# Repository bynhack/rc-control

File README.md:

# rc-control

**English** | [繁體中文](README.zh-TW.md) | [简体中文](README.zh-CN.md)

Drive RC cars with a sim-racing wheel and pedals. Plug the wheel into a 7" ESP32-P4 touch screen: it reads the wheel over USB, runs a driving model with ignition, gears, coasting and a real brake, and sends the result to the car over the radio that car uses. You don't need a PC.

## Features

- **Standalone wheel controller.** Built on the ESP32-P4 7" touch board with a MOZA R5 or Thrustmaster T300RS wheel base, picked on the screen.
- **Three ways to reach the car**, chosen per car:
  - ExpressLRS (CRSF)
  - a 4-in-1 MULTI module, over its serial protocol or as PPM
  - the toy car's own stock remote, with its pots driven by a DAC
- **Per-car handling** that every radio goes through. You set the steering range, expo, steering and throttle dead bands, trim, end points and reverse on the wheel itself.
- **Driving like a car.** Ignition, gears R N 1 2 3, coasting, a real brake, and an automatic brake-then-reverse sequence for the ESC.
- **Force feedback** on both bases (USB PID on the MOZA, Thrustmaster's protocol on the T300). Centring gets stronger with speed, and a soft stop marks the steering lock.
- **Dashboard.** Two instrument clusters with Simplified and Traditional Chinese text, six car profiles, and engine sound synthesised live on the board's speaker.
- **The car side.** The X2201's main board (KiCad: ESP32-S3, a brushed ESC and a 5 V BEC on board, push-button power), IR lap transponders and a finish-line arch, and 3D-printable parts for the wheel stand and the car.

## Documentation

| | |
|---|---|
| [Wheel controller](docs/en/wheel-controller.md) | Hardware, wiring, building and flashing the firmware |
| [Driving and handling](docs/en/driving.md) | Buttons, the driving model, cars, the handling settings, force feedback |
| [Radios](docs/en/radios.md) | ExpressLRS, MULTI 4-in-1, the toy remote |
| [Converting a toy remote](docs/en/toy-remote.md) | Driving a toy car's stock remote with an MCP4728 DAC |
| [Hardware](docs/en/hardware.md) | 3D-printed parts and the X2201 main board |
| [Lap-timing arch](docs/en/lap-arch.md) | The finish-line arch: receivers, wiring, firmware, lap events |
| [Development](docs/en/development.md) | Code layout, serial console, tuning page, regenerating fonts and assets |

## Quick start

```bash
git clone https://github.com/bynhack/rc-control.git
cd rc-control/firmware/wheel-controller
. ~/esp/esp-idf/export.sh          # ESP-IDF v5.5
idf.py build
idf.py -p /dev/cu.usbmodemXXXX flash
```

Then wire up a radio ([Radios](docs/en/radios.md)), plug the wheel into the board's USB-A port, and press Start on the wheel to start the engine.

## Repository layout

```
firmware/
  wheel-controller/     the wheel controller on the ESP32-P4 (ESP-IDF, C)
    main/               firmware source
    tools/              remote_tune.html, a Web Serial bench page
    design/             the dashboard artwork
  lap-arch/             the finish-line lap-timing arch (ESP32-C3)
  transponder/          the IR lap transponder for cars without the main board (CH32V003)
hardware/               boards (KiCad, generated by Python)
  PLAN.md               the X2201's confirmed hardware plan
  x2201-mainboard/      the X2201 main board
  transponder/          the transponder board
cad/                    3D-printable parts (Python, manifold3d)
docs/                   documentation in three languages
```

## Contributing

Issues and pull requests are welcome. Before you open a pull request, build the firmware with `idf.py build`. New documentation goes into all three languages under `docs/`. If you can only write one, say so in the pull request and someone will translate it.

## License

This project is released under **GPL-3.0-only** ([LICENSE](LICENSE)). That covers the firmware, the 3D models and the hardware design. If you distribute a modified version, including firmware flashed onto a device, you must offer its source under the same license.

Third-party code and assets keep their own licenses:

| Part | Where | License |
|---|---|---|
| ESP-IDF usb_host_hid, with interrupt OUT reports added | `firmware/wheel-controller/components/usb_host_hid` | Apache-2.0 |
| ESP-IDF, LVGL, the Waveshare BSP and other components | downloaded by the ESP-IDF component manager | Apache-2.0 / MIT etc. |
| Noto Sans SC, Saira, Barlow Condensed (rendered glyphs) | `firmware/wheel-controller/main/fonts` | SIL Open Font License 1.1 |

MOZA, Thrustmaster, ExpressLRS, Waveshare and other names only say which hardware works with this project. The project has no affiliation with them.

**Disclaimer:** RC cars are fast and heavy, and these modifications involve batteries and radio transmitters. You are responsible for any damage or injury that comes from following this project. Follow your local radio regulations.

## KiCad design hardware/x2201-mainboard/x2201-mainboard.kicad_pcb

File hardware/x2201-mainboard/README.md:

# X2201 主板

元件、電路、GPIO 和接口見 [../PLAN.md](../PLAN.md)。這裡只寫這塊板子的外形、擺位和焊接方式。

40×40 mm，2 層，1.6 mm。放在底盤 40×60 mm 的可用範圍內（沿車身 40、橫向 60）。

## 固定

座標以俯視為準：X 是橫向，Y 是沿車身，Y = 0 是車頭那邊的板邊，Y = 40 是車尾。

| 孔 | 位置 | 孔徑 | 說明 |
|---|---|---|---|
| MH1 M2 固定孔 | (22.28, 29.71)，偏車尾 | 2.4 mm 不鍍銅 | 鎖在底盤 M2 凸台上（凸台外徑 4.95），唯一的固定點 |
| MH2 定位孔 | (28.71, 7.68)，靠車頭 | 3.6 mm 不鍍銅 | 定位柱頂端的 3.5 插進來，不鎖螺絲 |

兩孔沿車身相距 22.02、橫向相距 6.43。2026-11-17 用 3D 列印的假板在車上試裝確認（假板和孔距測試板已刪除，需要時從 git 找回，commit `a1125d9`）。M2 凸台和定位柱頂面一樣高，板子平放在兩者上，不用墊。兩孔周圍 ±2.7 mm 不鋪銅、不放零件。

## 擺位

- 左側、車尾：SuperMini，USB-C 從車尾板邊伸出。它底下（零件最高 1.1 mm）有陀螺儀、電量分壓、D3，天線後面是圖傳電源開關（Q2、Q3），靠車尾那端是 IR LED 的驅動（Q4、R6、R8）。SuperMini 朝車頭那端是晶片天線，底下不鋪銅。
- 車頭板邊：BAT− / BAT+ 焊盤（左邊是 −、右邊是 +）、Q1 防反接、J7 馬達插座（插口朝車頭）。
- 中間：DRV8874 電調（緊貼馬達插座後面）、5V 降壓、按鈕電路、圖傳開關。
- 右板邊（插口朝外）：從車頭到車尾依序是 P2 舵機、J2 EP2、J3 圖傳。
- 車尾板邊：SuperMini 右邊是計圈用的 IR LED（D6，3 mm 直插）；右後角是 J8，4 個 2.54 mm 排針孔，讓 EP2 直接焊上、伸出車尾板邊（那裡沒有金屬遮擋）。J8 和 J2 接的是同一組訊號，兩個擇一用。
- 左板邊、車頭段（插口朝外）：J4 風扇、J6 按鈕。

## 焊接

JLC 貼正面所有的貼片零件，插座也包括在內。D6 紅外 LED（億光 IR204/H60，LCSC C60099，3 mm 直插）也放進 BOM，下單時要選插件（THT）焊接；不想付插件費的話，在 BOM 裡刪掉 D6 那一行自己焊。D6 立著焊、朝上，要換別的 LED 時，短腳（陰極）插方形焊盤。以下自己焊：

| 位號 | 內容 |
|---|---|
| U1 | ESP32-S3 SuperMini，兩排 9 針排針。**要用排針墊高約 2.5 mm，不能貼平焊**，底下有零件。方形焊盤是 5V 腳 |
| BAT+ / BAT− | 電池線，20 AWG，鑽孔 1.15 mm，在車頭板邊 |
| J8 | EP2 直焊孔。EP2 元件面朝上、焊盤那一邊朝主板、本體伸出車尾。從左到右：1 GND、2 5V、3 EP2 的 TX、4 EP2 的 RX（正反面印 −、+、T、R），剛好對上 EP2 焊盤（元件面朝上、焊盤朝自己時，由左到右是 RX、TX、5V、GND）。J8 腳距 2.54，焊之前量一下 EP2 焊盤的間距 |

**焊電池前先用萬用表確認正負極**。俯視時 BAT− 在左、BAT+ 在右，正反面都有標示。

## 下單前要確認

- U2 陀螺儀是 LSM6DSV16X（ST，C5267406），只能用**標準型**貼片（這個系列都一樣），下單時選標準型 PCBA。它在 SuperMini 正下方，下單後沒辦法自己換。
- D4 換成了另一顆料（1N4148WS，C2128），JLC 的 3D 模型可能不同，預覽裡要重看 D4。正確方向：D3 色帶（陰極）朝左板邊，也就是朝 SuperMini 的方形焊盤；D4、D5 色帶朝車尾，背向 DRV8874。
- 如果 JLC 要加工藝邊，選上下（車頭、車尾），不要選左右：左右兩邊的側插插座本體超出板邊約 0.1 mm。
- J2、J3 都是 ZH1.5 4P，插錯會燒壞 EP2 或圖傳；J4、J6 都是 2P。線材要做記號。
- 只能焊 SuperMini。備用的 S3-Zero 孔位一樣，但 5V、GND、3V3 在另一排，直接焊上去會燒，見 PLAN.md。
- 在 JLC 預覽裡，每顆有方向的零件（Q1–Q6、U2、U4、U5）的粉紅色第 1 腳圓點，都要落在絲印三角形那一角。
- D6 在預覽裡，LED 的「+」（陽極、長腳）要在右邊的圓形焊盤，「−」在左邊的方形焊盤。
- 在 JLC 的貼片預覽裡核對側插插座（P2、J2、J3、J4、J6、J7）、Q1、U4、U5、L1 的方向，插座的插口要朝板外。SOT-23（Q2、Q3、Q4、Q6）和 B5819WS（D3、D5）的角度修正是 v8 時在預覽裡核對過的。D4 換成 1N4148WS 後，JLC 用的是另一個 3D 模型，零度方向和 B5819WS 差 180°，CPL 已單獨修正，預覽裡還是要看一次（見本節第一條）。

## 下一版要改

這一版先不動佈局，下一版再改：

- D5 和 EN 之間串約 22k，根治只插 USB 時 EN 超過規格的問題。
- 地線有瓶頸，要多加 GND 過孔：
  - 馬達回流從頂層主地只經 2 個過孔到底層，再經 3 個過孔到 Q1 的 source。
  - C16（VM 的 100nF）的地在 Q1 那一小塊，離 PGND 很遠。
  - U4 的 GND 腳要經 1 + 1 個過孔才回到主地。
  - SuperMini、陀螺儀、IR 驅動的地，只靠一條 0.3 mm 的線接回主地。
- 可選：R26 改 2.2k，ITRIP 約 3.3A，比較接近 J7（PH2.0）的 2A 額定，也比較不會進過熱保護。

## 檔案

- `gen_pcb.py` 產生佈局，`gen_sch.py` 從佈局產生原理圖，兩邊的網路名稱一致。
- `x2201-mainboard-gerber.zip`、`bom.csv`、`cpl.csv` 是下單 JLC 用的檔案。

```bash
/Applications/KiCad/KiCad.app/Contents/Frameworks/Python.framework/Versions/Current/bin/python3 gen_pcb.py
```

佈線用 `../tools/freerouting-1.9.0.jar`。佈線前會先畫好 `HAND_T` 裡手畫的線（降壓、陀螺儀、DRV8874 的馬達輸出、VM、接地、IR）。加 `REUSE_SES=1` 會沿用已存的 `.ses`，`FAB=1` 會輸出 Gerber、BOM 和 CPL。之後執行 `gen_sch.py` 更新原理圖。

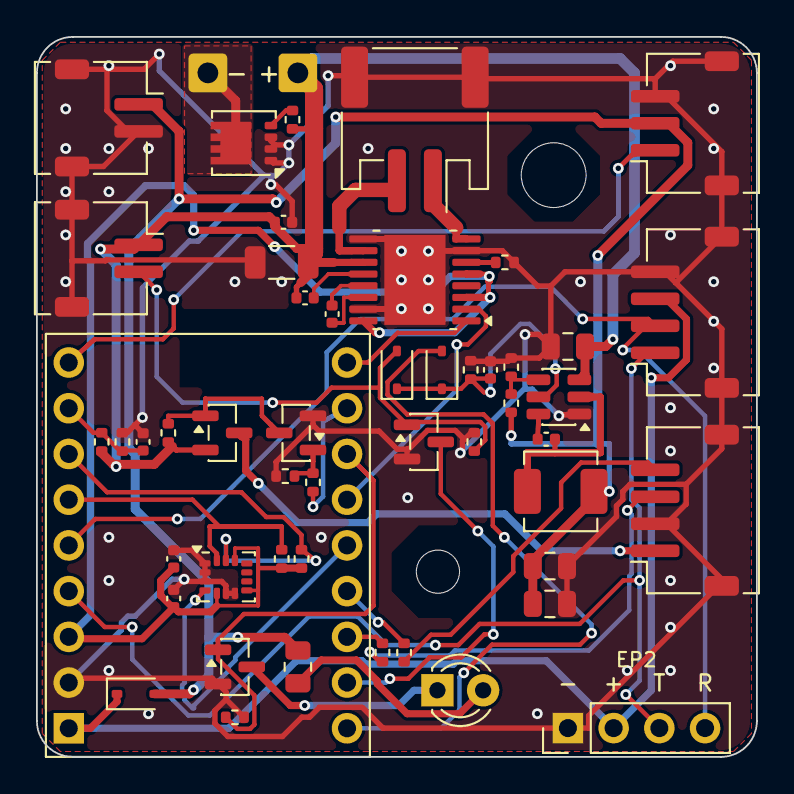
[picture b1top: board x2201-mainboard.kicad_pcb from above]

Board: 2 copper layers, 40.0 x 40.0 mm, 54 parts (0 on the bottom side), 40 nets.

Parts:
C1: 10uF; C_0805_2012Metric
C3, C4: 22uF; C_0805_2012Metric
C5, C11, C12, C13, C16, C18, C20: 100nF; C_0402_1005Metric
C15: 22uF 25V; C_1206_3216Metric
C19: 22nF; C_0402_1005Metric
D3, D5: B5819WS; D_SOD-323
D4: 1N4148WS; D_SOD-323
D6: IR 940nm 3mm; LED_D3.0mm
J2: ZH1.5 4P side (EP2); JST_ZH_S4B-ZR-SM4A-TF_1x04-1MP_P1.50mm_Horizontal
J3: ZH1.5 4P side (VTX); JST_ZH_S4B-ZR-SM4A-TF_1x04-1MP_P1.50mm_Horizontal
J4: ZH1.5 2P side (fan); JST_ZH_S2B-ZR-SM4A-TF_1x02-1MP_P1.50mm_Horizontal
J6: ZH1.5 2P side (button); JST_ZH_S2B-ZR-SM4A-TF_1x02-1MP_P1.50mm_Horizontal
J7: ZH2.0 2P side (motor); JST_PH_S2B-PH-SM4-TB_1x02-1MP_P2.00mm_Horizontal
J8: EP2 pads; PinHeader_1x04_P2.54mm_Vertical
L1: 4.7uH; L_Changjiang_FXL0420
MH1, MH2: M2 hole
P2: ZH1.5 3P side (servo); JST_ZH_S3B-ZR-SM4A-TF_1x03-1MP_P1.50mm_Horizontal
Q1: DMN3008SFG-7; Diodes_PowerDI3333-8
Q2: AO3401; SOT-23
Q3, Q4, Q6: AO3400; SOT-23
R1, R28: 10k; R_0402_1005Metric
R2, R7, R8, R14, R16: 100k; R_0402_1005Metric
R3, R15: 22k; R_0402_1005Metric
R4, R19, R20: 1k; R_0402_1005Metric
R5: 3k; R_0402_1005Metric
R6: 33; R_0805_2012Metric
R9, R10: 4.7k; R_0402_1005Metric
R26: 1.5k; R_0402_1005Metric
U1: ESP32-S3 SuperMini
U2: LSM6DSV16X; LGA-14_3x2.5mm_P0.5mm_LayoutBorder3x4y
U4: LMR51430XDDCR; SOT-23-6
U5: DRV8874PWPR; HTSSOP-16-1EP_4.4x5mm_P0.65mm_EP3.4x5mm_Mask2.46x2.31mm
W1: BAT+; SolderWire-0.5sqmm_1x01_D0.9mm_OD2.1mm
W2: BAT-; SolderWire-0.5sqmm_1x01_D0.9mm_OD2.1mm

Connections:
3V3: C12.1, C13.1, R9.1, R10.1, U1.3, U2.5, U2.8, U2.12, U5.3, U5.5, U5.16
5V: C3.1, C4.1, D3.2, J4.1, L1.2, P2.2, R3.1, R6.2
BAT_N: Q1.5, W2.1
BTN: D4.2, J6.2, Q6.1, R28.1
BTN_SENSE: Q6.3, U1.11
CB: C5.1, U4.6
CPH: C19.2, U5.13
CPL: C19.1, U5.14
CRSF_RX: J2.1, J8.3, U1.4
CRSF_TX: J2.2, J8.4, U1.5
EN_SW: C20.1, D4.1, D5.1, R16.1, U4.5
FB: R3.2, R5.1, U4.4
GND: C1.2, C3.2, C4.2, C11.2, C12.2, C13.2, C15.2, C16.2, C20.2, J2.4, J2.MP, J3.2, J3.MP, J4.2, J4.MP, J6.MP, J7.MP, J8.1, P2.3, P2.MP, Q1.1, Q1.2, Q1.3, Q3.2, Q4.2, Q6.2, R5.2, R7.2, R8.2, R15.2, R16.2, R26.2, R28.2, U1.2, U2.1, U2.2, U2.3, U2.6, U2.7, U4.1, U5.7, U5.9, U5.15, U5.17
HOLD: D5.2, U1.10
IMU_INT: U1.14, U2.4
IPROPI: R26.1, U5.6
IR: Q4.1, R8.1, U1.16
LEDA: D6.2, R6.1
LEDK: D6.1, Q4.3
MOT_A: J7.1, U5.8
MOT_B: J7.2, U5.10
MSP_RX: R20.1, U1.13
MSP_TX: R19.1, U1.12
M_FWD: U1.18, U5.1
M_REV: U1.15, U5.2
Q1G: Q1.4, R1.2
Q2G: Q2.1, Q3.3, R2.1
Q3G: Q3.1, R4.2, R7.1
SCL: R10.2, U1.7, U2.13
SDA: R9.2, U1.6, U2.14
SERVO: P2.1, U1.9
SW: C5.2, L1.1, U4.2
VBAT: C1.1, C15.1, C16.1, C18.1, J6.1, Q2.2, R1.1, R2.2, R14.1, U4.3, U5.11, W1.1
VBAT_ADC: C11.1, R14.2, R15.1, U1.8
VCP: C18.2, U5.12
VIN: D3.1, J2.3, J8.2, U1.1
VTX: J3.1, Q2.3
VTX_EN: R4.1, U1.17
VTX_RX: J3.3, R19.2
VTX_TX: J3.4, R20.2

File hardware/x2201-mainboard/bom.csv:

Comment,Designator,Footprint,Qty,LCSC Part #
10uF,C1,C_0805_2012Metric,1,C15850
22uF 25V,C15,C_1206_3216Metric,1,C12891
22nF,C19,C_0402_1005Metric,1,C1532
22uF,"C3,C4",C_0805_2012Metric,2,C45783
100nF,"C11,C12,C13,C16,C18,C20,C5",C_0402_1005Metric,7,C1525
1N4148WS,D4,D_SOD-323,1,C2128
B5819WS,"D3,D5",D_SOD-323,2,C7420331
IR 940nm 3mm,D6,LED_D3.0mm,1,C60099
ZH1.5 4P side (EP2),J2,JST_ZH_S4B-ZR-SM4A-TF_1x04-1MP_P1.50mm_Horizontal,1,C485354
ZH1.5 4P side (VTX),J3,JST_ZH_S4B-ZR-SM4A-TF_1x04-1MP_P1.50mm_Horizontal,1,C485354
ZH1.5 2P side (fan),J4,JST_ZH_S2B-ZR-SM4A-TF_1x02-1MP_P1.50mm_Horizontal,1,C265329
ZH1.5 2P side (button),J6,JST_ZH_S2B-ZR-SM4A-TF_1x02-1MP_P1.50mm_Horizontal,1,C265329
ZH2.0 2P side (motor),J7,JST_PH_S2B-PH-SM4-TB_1x02-1MP_P2.00mm_Horizontal,1,C295747
4.7uH,L1,L_Changjiang_FXL0420,1,C167208
ZH1.5 3P side (servo),P2,JST_ZH_S3B-ZR-SM4A-TF_1x03-1MP_P1.50mm_Horizontal,1,C72591
DMN3008SFG-7,Q1,Diodes_PowerDI3333-8,1,C384563
AO3401,Q2,SOT-23,1,C15127
AO3400,"Q3,Q4,Q6",SOT-23,3,C20917
4.7k,"R10,R9",R_0402_1005Metric,2,C25900
1k,"R19,R20,R4",R_0402_1005Metric,3,C11702
1.5k,R26,R_0402_1005Metric,1,C25867
10k,"R1,R28",R_0402_1005Metric,2,C25744
22k,"R15,R3",R_0402_1005Metric,2,C25768
3k,R5,R_0402_1005Metric,1,C25784
33,R6,R_0805_2012Metric,1,C17634
100k,"R14,R16,R2,R7,R8",R_0402_1005Metric,5,C25741
LSM6DSV16X,U2,LGA-14_3x2.5mm_P0.5mm_LayoutBorder3x4y,1,C5267406
LMR51430XDDCR,U4,SOT-23-6,1,C5185863
DRV8874PWPR,U5,HTSSOP-16-1EP_4.4x5mm_P0.65mm_EP3.4x5mm_Mask2.46x2.31mm,1,C1855818

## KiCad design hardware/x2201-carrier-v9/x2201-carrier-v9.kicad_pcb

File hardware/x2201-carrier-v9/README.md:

# X2201 主板 v9（階段 1，舊電源方案）

**不要打板。** 2026-11-13 決定階段 1 把有刷電調做在主板上，不外掛電調；BEC 用本板這顆 5V 3A 降壓，供應 1–3A。本目錄的電調仍是外接焊盤，電池銅皮也是按外接大電流電調畫的。訊號、插座、GPIO 和 U4 降壓可以沿用，見 [ROADMAP.md](../ROADMAP.md)。

49×38 mm，2 層，1.6 mm，單面零件，4 個 M2 不鍍銅孔（孔距 44×33）。

電池接到主板，主板再接外接電調、舵機、EP2 和圖傳。電調只負責驅動馬達，可以換成任何標準有刷電調，例如 MINI30A。

## 接法

```
電池 → W1/W2 → Q1 防反接 ─┬→ W3/W4 → 外接電調 → 馬達
                           ├→ U4 5V 3A 降壓 → S3、EP2、舵機、風扇、IR
                           └→ 電量偵測、圖傳（S3 控制開關）
EP2 ─CRSF→ J2 → S3 ─┬─ PWM → P2 舵機
                    └─ PWM → P1 電調訊號
陀螺儀 LSM6DS3TR-C ─I2C→ S3
```

- **防反接 Q1**：N-MOS 放在電池負極，導通電阻約 5.5 mΩ。電池接反時整台車都斷開，**連電調也受保護**。
- **5V 由主板供應**：電調的 BEC 不接（P1 第 2 腳空著），避免兩個 5V 互相打架。
- **只插 USB 時**：S3 和 EP2 有電，可以直接調試；舵機、風扇、IR、圖傳沒有電。
- **EP2 的 TX 焊盤只接 S3 的輸入腳**，原本上電卡死的條件不存在。

## 焊接

板上零件全部貼片。要自己焊的只有：

| 位號 | 內容 |
|---|---|
| W1 BAT+、W2 BAT− | 電池線，外側一排（標示 BAT） |
| W3 ESC+、W4 ESC− | 電調電源線，內側一排（標示 ESC） |
| P1、P2 | 2.54 mm 3 針排針 |

焊線孔孔徑 1.25 mm，適合 20 AWG 左右的線。**焊電池前用萬用表確認正負極**：上排是 +，下排是 −。

## 插座

| 位號 | 類型 | 腳位 |
|---|---|---|
| P1 電調訊號 | 2.54 3P 排針 | 1 訊號、2 不接（電調 BEC）、3 GND |
| P2 舵機 | 2.54 3P 排針 | 1 訊號、2 5V、3 GND |
| J2 EP2 | ZH1.5 4P | 1 EP2 TX、2 EP2 RX、3 5V、4 GND |
| J3 圖傳 | JST1.0（SH）6P | 1 電源、2 GND、3 圖傳 RX、4 圖傳 TX，5、6 不接 |
| J4 風扇 | ZH1.5 2P | 1 5V、2 GND，接上電池就轉 |
| J5 IR | ZH1.5 2P | 1 LED+、2 LED− |
| J9 | USB-C | 燒錄與除錯 |

排針第 1 腳是方形焊盤。

## GPIO

| GPIO | 功能 |
|---|---|
| 6 | 圖傳電源，高電位開，重開機時關閉 |
| 7 | 電調油門 PWM（10k 下拉：S3 重開機時電調收不到脈衝，馬達停住） |
| 8 | 舵機 PWM |
| 9 | 電池電壓（×22/122） |
| 10 / 11 | 圖傳 UART RX / TX |
| 13 / 14 | CRSF RX / TX |
| 15 | IR |
| 16 / 17 / 18 | 陀螺儀 SDA / SCL / INT（I2C 位址 0x6A） |

油門、舵機、CRSF 的腳位和 `firmware/elrs-bench` 相同。B、G 兩個焊盤用來救磚：短接 B 和 G 同時上電，進入下載模式。

## 設計說明

- **主電流路徑**：電池焊盤到電調焊盤之間，正負極都用雙面覆銅連接，不經過細走線。電流上限依電調規格（30A，峰值 40A）設計，但 500 mAh 電池實際能持續供應的電流遠低於此。
- **降壓**：LMR51430，輸出 5.0V（0.6V × (1 + 22k/3k)），電感 4.7µH。EN 在晶片底下直接接 VIN，接地走晶片底下的過孔，SW 往外繞到電感：這幾段是手畫的，見 `gen_pcb.py` 的 `HAND_T`。
- **舵機**：插座旁有 22µF 電容，吸收舵機用力時的電流突波。

## 尚未驗證

- 整塊板子都還沒有實機驗證。
- 新零件（Q1、U4、U2、L1、P1、P2）的貼片方向還沒有在預覽裡核對。
- 沒有做外殼和車內空間的干涉檢查。

## 重新產生

```bash
/Applications/KiCad/KiCad.app/Contents/Frameworks/Python.framework/Versions/Current/bin/python3 gen_pcb.py
```

佈線用 `../tools/freerouting-1.9.0.jar`；沒有這個檔案時加 `REUSE_SES=1`，沿用已存的 `.ses`。`FAB=1` 同時輸出 Gerber、BOM 和座標檔，之後再跑 `gen_sch.py` 更新原理圖。

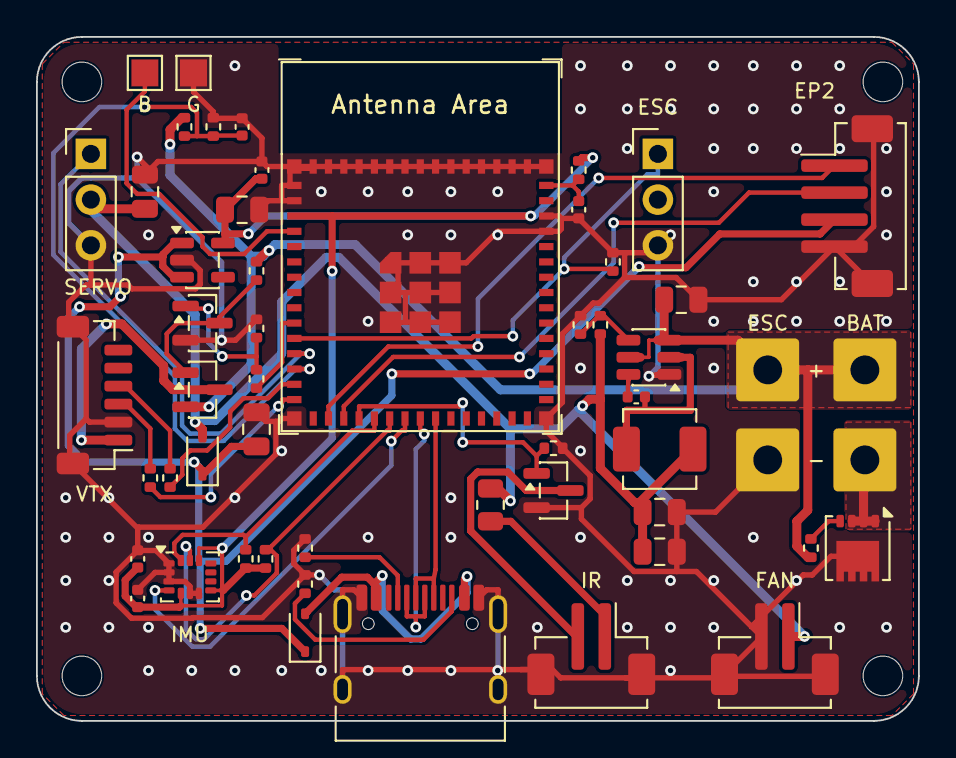
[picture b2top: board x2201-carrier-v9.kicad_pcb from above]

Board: 2 copper layers, 49.0 x 38.0 mm, 58 parts (0 on the bottom side), 36 nets.

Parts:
C1: 10uF; C_0805_2012Metric
C3, C4, C9, C10, C14: 22uF; C_0805_2012Metric
C5, C6, C11, C12, C13: 100nF; C_0402_1005Metric
C8: 1uF; C_0402_1005Metric
D2, D3: B5819WS; D_SOD-323
J2: ZH1.5 4P (EP2); JST_ZH_B4B-ZR-SM4-TF_1x04-1MP_P1.50mm_Vertical
J3: SH1.0 6P (VTX); JST_SH_BM06B-SRSS-TB_1x06-1MP_P1.00mm_Vertical
J4: ZH1.5 2P (fan); JST_ZH_B2B-ZR-SM4-TF_1x02-1MP_P1.50mm_Vertical
J5: ZH1.5 2P (IR LED); JST_ZH_B2B-ZR-SM4-TF_1x02-1MP_P1.50mm_Vertical
J9: USB-C; USB_C_Receptacle_HRO_TYPE-C-31-M-12
L1: 4.7uH; L_Changjiang_FXL0420
MH1, MH2, MH3, MH4: M2 hole
P1: 2.54 3P (ESC); PinHeader_1x03_P2.54mm_Vertical
P2: 2.54 3P (servo); PinHeader_1x03_P2.54mm_Vertical
Q1: DMN3008SFG-7; Diodes_PowerDI3333-8
Q2: AO3401; SOT-23
Q3, Q4: AO3400; SOT-23
R1, R11, R21: 10k; R_0402_1005Metric
R2, R7, R8, R14: 100k; R_0402_1005Metric
R3, R15: 22k; R_0402_1005Metric
R4, R19, R20: 1k; R_0402_1005Metric
R5: 3k; R_0402_1005Metric
R6: 33; R_0805_2012Metric
R9, R10: 4.7k; R_0402_1005Metric
R12, R13: 5.1k; R_0402_1005Metric
TP1: BOOT; TestPoint_Pad_1.5x1.5mm
TP3: G; TestPoint_Pad_1.5x1.5mm
U1: ESP32-S3-MINI-1-N8; ESP32-S3-MINI-1
U2: LSM6DS3TR-C; LGA-14_3x2.5mm_P0.5mm_LayoutBorder3x4y
U3: AP2112K-3.3; SOT-23-5
U4: LMR51430XDDCR; SOT-23-6
W1: BAT+; SolderWire-0.75sqmm_1x01_D1.25mm_OD3.5mm
W2: BAT-; SolderWire-0.75sqmm_1x01_D1.25mm_OD3.5mm
W3: ESC+; SolderWire-0.75sqmm_1x01_D1.25mm_OD3.5mm
W4: ESC-; SolderWire-0.75sqmm_1x01_D1.25mm_OD3.5mm

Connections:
3V3: C6.1, C10.1, C12.1, C13.1, R9.1, R10.1, R21.1, U1.3, U2.5, U2.8, U2.12, U3.5
5V: C3.1, C4.1, C14.1, D3.2, J4.1, L1.2, P2.2, R3.1, R6.2
BAT_N: Q1.1, Q1.2, Q1.3, W2.1
BOOT: TP1.1, U1.4
CB: C5.1, U4.6
CC1: J9.A5, R12.1
CC2: J9.B5, R13.1
CRSF_RX: J2.1, U1.17
CRSF_TX: J2.2, U1.18
EN: C8.1, R21.2, U1.45
FB: R3.2, R5.1, U4.4
GND: C1.2, C3.2, C4.2, C6.2, C8.2, C9.2, C10.2, C11.2, C12.2, C13.2, C14.2, J2.4, J2.MP, J3.2, J3.MP, J4.2, J4.MP, J5.MP, J9.A1, J9.A12, J9.B1, J9.B12, J9.SH, P1.3, P2.3, Q1.5, Q3.2, Q4.2, R5.2, R7.2, R8.2, R11.2, R12.2, R13.2, R15.2, TP3.1, U1.1, U1.2, U1.42, U1.43, U1.46, U1.47, U1.48, U1.49, U1.50, U1.51, U1.52, U1.53, U1.54, U1.55, U1.56, U1.57, U1.58, U1.59, U1.60, U1.61, U1.62, U1.63, U1.64, U1.65, U2.1, U2.2, U2.3, U2.6, U2.7, U3.2, U4.1, W4.1
IMU_INT: U1.22, U2.4
IR: Q4.1, R8.1, U1.19
LEDA: J5.1, R6.1
LEDK: J5.2, Q4.3
MSP_RX: R20.1, U1.14
MSP_TX: R19.1, U1.15
Q1G: Q1.4, R1.2
Q2G: Q2.1, Q3.3, R2.1
Q3G: Q3.1, R4.2, R7.1
SCL: R10.2, U1.21, U2.13
SDA: R9.2, U1.20, U2.14
SERVO: P2.1, U1.12
SW: C5.2, L1.1, U4.2
THR: P1.1, R11.1, U1.11
USB_DM: J9.A7, J9.B7, U1.23
USB_DP: J9.A6, J9.B6, U1.24
VBAT: C1.1, Q2.2, R1.1, R2.2, R14.1, U4.3, U4.5, W1.1, W3.1
VBAT_ADC: C11.1, R14.2, R15.1, U1.13
VBUS: D2.2, J9.A4, J9.A9, J9.B4, J9.B9
VIN: C9.1, D2.1, D3.1, J2.3, U3.1, U3.3
VTX: J3.1, Q2.3
VTX_EN: R4.1, U1.10
VTX_RX: J3.3, R19.2
VTX_TX: J3.4, R20.2

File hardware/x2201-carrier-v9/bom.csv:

Comment,Designator,Footprint,Qty,LCSC Part #
10uF,C1,C_0805_2012Metric,1,C15850
22uF,"C10,C14,C3,C4,C9",C_0805_2012Metric,5,C45783
100nF,"C11,C12,C13,C5,C6",C_0402_1005Metric,5,C1525
1uF,C8,C_0402_1005Metric,1,C52923
B5819WS,"D2,D3",D_SOD-323,2,C7420331
ZH1.5 4P (EP2),J2,JST_ZH_B4B-ZR-SM4-TF_1x04-1MP_P1.50mm_Vertical,1,C265083
SH1.0 6P (VTX),J3,JST_SH_BM06B-SRSS-TB_1x06-1MP_P1.00mm_Vertical,1,C160392
ZH1.5 2P (fan),J4,JST_ZH_B2B-ZR-SM4-TF_1x02-1MP_P1.50mm_Vertical,1,C265284
ZH1.5 2P (IR LED),J5,JST_ZH_B2B-ZR-SM4-TF_1x02-1MP_P1.50mm_Vertical,1,C265284
USB-C,J9,USB_C_Receptacle_HRO_TYPE-C-31-M-12,1,C165948
4.7uH,L1,L_Changjiang_FXL0420,1,C167208
DMN3008SFG-7,Q1,Diodes_PowerDI3333-8,1,C384563
AO3401,Q2,SOT-23,1,C15127
AO3400,"Q3,Q4",SOT-23,2,C20917
10k,"R1,R11,R21",R_0402_1005Metric,3,C25744
4.7k,"R10,R9",R_0402_1005Metric,2,C25900
5.1k,"R12,R13",R_0402_1005Metric,2,C25905
22k,"R15,R3",R_0402_1005Metric,2,C25768
1k,"R19,R20,R4",R_0402_1005Metric,3,C11702
3k,R5,R_0402_1005Metric,1,C25784
33,R6,R_0805_2012Metric,1,C17634
100k,"R14,R2,R7,R8",R_0402_1005Metric,4,C25741
ESP32-S3-MINI-1-N8,U1,ESP32-S3-MINI-1,1,C2913206
LSM6DS3TR-C,U2,LGA-14_3x2.5mm_P0.5mm_LayoutBorder3x4y,1,C967633
AP2112K-3.3,U3,SOT-23-5,1,C51118
LMR51430XDDCR,U4,SOT-23-6,1,C5185863

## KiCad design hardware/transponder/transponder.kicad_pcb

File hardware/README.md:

# hardware

Boards for the cars (KiCad). 車上用的電路板 · 车上用的电路板

- [PLAN.md](PLAN.md): the X2201's confirmed hardware plan, the parts and the wiring. The board's shape can change to suit the car; the parts and wiring follow this.
- [ROADMAP.md](ROADMAP.md): where the boards are going.
- [`x2201-mainboard`](x2201-mainboard): the X2201 main board, 40 × 40 mm, on one M2 screw and a locating post. ESP32-S3 SuperMini, DRV8874 brushed ESC, 5 V buck (about 2–2.5 A), side-entry ZH plugs, push-button power, the IR LED on board. Ordered from JLC on 2026-11-17 (commit `a1125d9`).
- [`transponder`](transponder): the lap-timing transponder on its own, for the other cars.

Earlier boards (v3 to v9) were removed on 2026-11-16; they're in git history up to commit `56bd000`.

Docs: [English](../docs/en/hardware.md#x2201-main-board) · [繁體中文](../docs/zh-TW/hardware.md#x2201-主板) · [简体中文](../docs/zh-CN/hardware.md#x2201-主板)

`pcbgen.py` and `schgen.py` are the helpers the boards' `gen_pcb.py` / `gen_sch.py` share. `lib/` holds symbols KiCad doesn't ship. See [lib/README.md](lib/README.md).

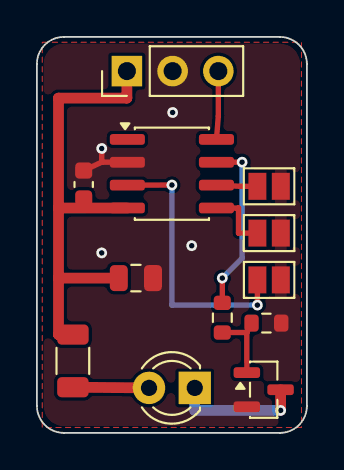
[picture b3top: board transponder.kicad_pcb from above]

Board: 2 copper layers, 15.0 x 22.0 mm, 12 parts (0 on the bottom side), 10 nets.

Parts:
C1: 100nF; C_0603_1608Metric
C2: 10uF; C_0805_2012Metric
D1: IR 940nm 3mm; LED_D3.0mm
J1: 5V GND SWIO; PinHeader_1x03_P2.54mm_Vertical
JP1: ID0; SolderJumper-2_P1.3mm_Open_Pad1.0x1.5mm
JP2: ID1; SolderJumper-2_P1.3mm_Open_Pad1.0x1.5mm
JP3: ID2; SolderJumper-2_P1.3mm_Open_Pad1.0x1.5mm
Q1: AO3400; SOT-23
R1: 33; R_1206_3216Metric
R2: 100; R_0603_1608Metric
R3: 100k; R_0603_1608Metric
U1: CH32V003J4M6; SOIC-8_3.9x4.9mm_P1.27mm

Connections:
5V: C1.2, C2.1, J1.1, R1.2, U1.4
GATE: Q1.1, R2.2, R3.1
GND: C1.1, C2.2, J1.2, JP1.2, JP2.2, JP3.2, Q1.2, R3.2, U1.2
ID0: JP1.1, U1.5
ID1: JP2.1, U1.6
ID2: JP3.1, U1.3
LEDA: D1.2, R1.1
LEDK: D1.1, Q1.3
PWM: R2.1, U1.7
SWIO: J1.3, U1.8

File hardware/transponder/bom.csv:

Comment,Designator,Footprint,Qty,LCSC Part #
100nF,C1,C_0603_1608Metric,1,C14663
10uF,C2,C_0805_2012Metric,1,C15850
AO3400,Q1,SOT-23,1,C20917
33,R1,R_1206_3216Metric,1,
100,R2,R_0603_1608Metric,1,C22775
100k,R3,R_0603_1608Metric,1,C25803
CH32V003J4M6,U1,SOIC-8_3.9x4.9mm_P1.27mm,1,C5299908

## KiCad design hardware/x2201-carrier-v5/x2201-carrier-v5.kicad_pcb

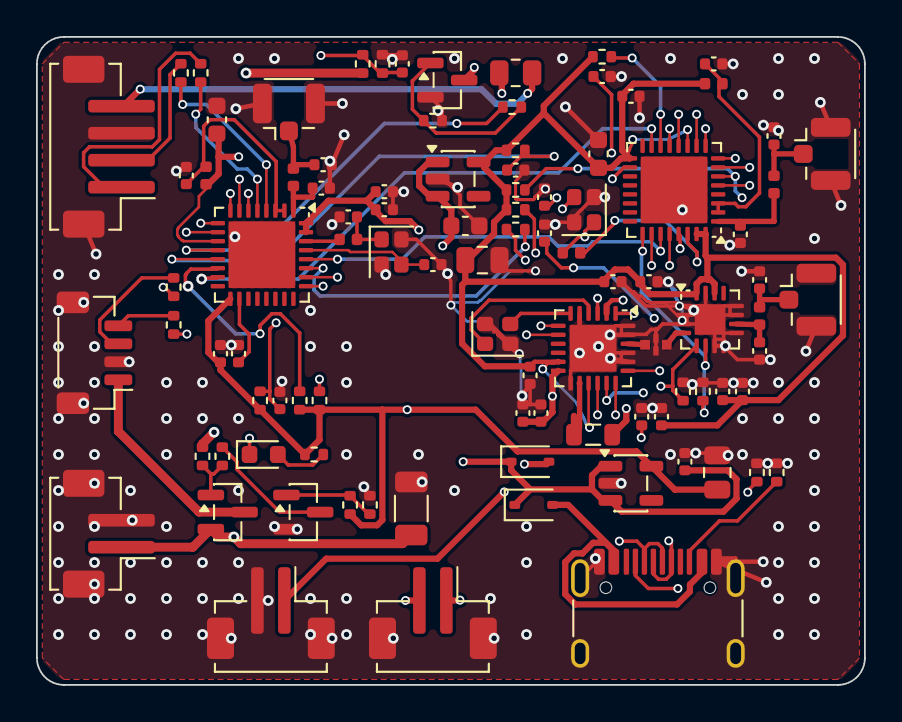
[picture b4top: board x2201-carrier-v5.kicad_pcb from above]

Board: 4 copper layers, 46.0 x 36.0 mm, 96 parts (0 on the bottom side), 70 nets.

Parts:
C3: 22uF 25V; C_1206_3216Metric
C8, C9, C18, C22, C25, C26, C42, C45, C49: 1uF; C_0402_1005Metric
C10, C17: 22uF; C_0805_2012Metric
C11, C21, C34, C35, C36, C44: 100nF; C_0402_1005Metric
C16: 1uF; C_0603_1608Metric
C19, C31, C33, C46: 10nF; C_0402_1005Metric
C20, C43: 10uF; C_0603_1608Metric
C27, C28, C37, C50, C51: 10pF; C_0402_1005Metric
C29, C30, C38, C39, C40, C41: 1.2pF; C_0402_1005Metric
C32: 470nF; C_0402_1005Metric
D2, D3: B5819WS; D_SOD-323
D4: green; LED_0603_1608Metric
FL1: 2450FM07D0034T; 2450FM07D0034
J1: ZH1.5 4P (ESC); JST_ZH_B4B-ZR-SM4-TF_1x04-1MP_P1.50mm_Vertical
J3: SH1.0 4P (VTX); JST_SH_BM04B-SRSS-TB_1x04-1MP_P1.00mm_Vertical
J4: ZH1.5 2P (fan); JST_ZH_B2B-ZR-SM4-TF_1x02-1MP_P1.50mm_Vertical
J5: ZH1.5 2P (IR LED); JST_ZH_B2B-ZR-SM4-TF_1x02-1MP_P1.50mm_Vertical
J6: ZH1.5 2P (battery); JST_ZH_B2B-ZR-SM4-TF_1x02-1MP_P1.50mm_Vertical
J9: USB-C; USB_C_Receptacle_HRO_TYPE-C-31-M-12
J10: U.FL (ELRS); U.FL_Hirose_U.FL-R-SMT-1_Vertical
J11: U.FL (receiver WiFi); U.FL_Hirose_U.FL-R-SMT-1_Vertical
J12: U.FL (brain WiFi); U.FL_Hirose_U.FL-R-SMT-1_Vertical
L2, L8: 2nH; L_0402_1005Metric
L3, L9: 24nH; L_0402_1005Metric
L4, L6, L7: 3nH; L_0402_1005Metric
L5: 15uH; L_0805_2012Metric
Q2: AO3401; SOT-23
Q3, Q4: AO3400; SOT-23
R2, R5, R8, R14, R31, R32: 100k; R_0402_1005Metric
R3: 47k; R_0402_1005Metric
R4, R18, R19, R20, R30: 1k; R_0402_1005Metric
R6: 33; R_0805_2012Metric
R7: 100; R_0402_1005Metric
R11, R25, R26, R27, R28, R29, R34: 10k; R_0402_1005Metric
R12, R13: 5.1k; R_0402_1005Metric
R15: 22k; R_0402_1005Metric
R16, R17: 220; R_0402_1005Metric
U1, U5: ESP32-C3FH4; QFN-32-1EP_5x5mm_P0.5mm_EP3.7x3.7mm
U3, U8: AP2112K-3.3; SOT-23-5
U6: SX1280IMLTRT; QFN-24-1EP_4x4mm_P0.5mm_EP2.6x2.6mm
U7: AT2401C; QFN-16-1EP_3x3mm_P0.5mm_EP1.7x1.7mm
Y1, Y3: 40MHz; Crystal_SMD_2016-4Pin_2.0x1.6mm
Y2: 52MHz; Crystal_SMD_2016-4Pin_2.0x1.6mm

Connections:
3V3: C10.1, C43.1, C44.1, C45.1, C46.1, L8.1, R4.1, R11.1, R18.1, R25.1, R34.1, U1.11, U1.17, U1.31, U1.32, U3.5
3V3R: C17.1, C18.1, C19.1, C20.1, C21.1, C34.1, C35.1, C36.1, C37.1, L2.1, R26.1, R27.1, R28.1, R29.1, U5.11, U5.17, U5.31, U5.32, U6.11, U6.15, U7.14, U7.16, U8.5
5V: D3.2, J1.4, J4.1, R6.2
B_ANT: C41.1, J12.1, L7.2
B_IO2: R25.2, U1.6
B_RF: C40.1, L7.1, U1.1
B_VPA: C42.1, L8.2, U1.2, U1.3
B_VSPI: C49.1, U1.18
B_XI: C51.1, L9.1, Y3.1
B_XN: C50.1, U1.29, Y3.3
B_XP: L9.2, U1.30
CC1: J9.A5, R12.1
CC2: J9.B5, R13.1
CRSF_RX: R30.2, U1.27
CRSF_TX: U1.28, U5.27
ELRS_ANT: C39.1, J10.1, L6.2
EN: C8.1, R11.2, U1.7
GATE: Q4.1, R7.2, R8.1
GND: C3.2, C8.2, C9.2, C10.2, C11.2, C16.2, C17.2, C18.2, C19.2, C20.2, C21.2, C22.2, C25.2, C26.2, C27.2, C28.2, C29.2, C30.2, C31.2, C32.2, C33.2, C34.2, C35.2, C36.2, C37.2, C38.2, C39.2, C40.2, C41.2, C42.2, C43.2, C44.2, C45.2, C46.2, C49.2, C50.2, C51.2, FL1.2, FL1.4, J1.3, J1.MP, J3.2, J3.MP, J4.2, J4.MP, J5.MP, J6.2, J6.MP, J9.A1, J9.A12, J9.B1, J9.B12, J9.SH, J10.2, J11.2, J12.2, Q3.2, Q4.2, R5.2, R8.2, R12.2, R13.2, R15.2, R31.2, R32.2, U1.33, U3.2, U5.33, U6.5, U6.13, U6.20, U6.21, U6.23, U6.24, U6.25, U7.1, U7.2, U7.3, U7.7, U7.8, U7.9, U7.11, U7.12, U7.15, U7.17, U8.2, Y1.2, Y1.4, Y2.2, Y2.4, Y3.2, Y3.4
IR: R7.1, U1.12
LED: D4.1, R34.2, U1.14
LEDA: J5.1, R6.1
LEDK: J5.2, Q4.3
LEDR: D4.2, R18.2
MSP_RX: R20.1, U1.10
MSP_TX: R19.1, U1.9
PA_ANT: C38.1, L6.1, U7.10
PA_IO: FL1.3, U7.4
PA_RXEN: R32.1, U5.25, U7.6
PA_TXEN: R31.1, U5.26, U7.5
Q2G: Q2.1, R2.1, R3.1
Q3D: Q3.3, R3.2
Q3G: Q3.1, R4.2, R5.1
RXC_ANT: C30.1, J11.1, L4.2
RXC_BOOT: R29.2, U1.15, U5.15
RXC_EN: C26.1, R26.2, U1.13, U5.7
RXC_IO8: R28.2, U5.14
RXC_RF: C29.1, L4.1, U5.1
RXC_TXD: R30.1, U5.28
RXC_VPA: C22.1, L2.2, U5.2, U5.3
RXC_VSPI: C25.1, U5.18
RXC_XI: C27.1, L3.1, Y1.1
RXC_XN: C28.1, U5.29, Y1.3
RXC_XP: L3.2, U5.30
RX_BUSY: U5.8, U6.7
RX_DIO1: U5.5, U6.8
RX_MISO: U5.10, U6.16
RX_MOSI: U5.9, U6.17
RX_NSS: U5.13, U6.19
RX_RST: R27.2, U5.6, U6.3
RX_SCK: U5.12, U6.18
S1: R16.1, U1.4
S1E: J1.2, R16.2
S2: R17.1, U1.5
S2E: J1.1, R17.2
SX_DCC: C32.1, C33.1, L5.2, U6.2, U6.12
SX_RF: FL1.1, U6.22
SX_SW: L5.1, U6.14
SX_VRPA: C31.1, U6.1
SX_XA: U6.4, Y2.1
SX_XB: U6.6, Y2.3
USB_DM: J9.A7, J9.B7, U1.25
USB_DP: J9.A6, J9.B6, U1.26
VBAT: C3.1, J6.1, Q2.2, R2.2, R14.1
VBAT_ADC: C11.1, R14.2, R15.1, U1.8
VBUS: D2.2, J9.A4, J9.A9, J9.B4, J9.B9
VIN: C9.1, C16.1, D2.1, D3.1, U3.1, U3.3, U8.1, U8.3
VTX: J3.1, Q2.3
VTX_RX: J3.3, R19.2
VTX_TX: J3.4, R20.2

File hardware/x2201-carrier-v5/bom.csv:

Comment,Designator,Footprint,Qty,LCSC Part #
22uF,"C10,C17",C_0805_2012Metric,2,C45783
1uF,C16,C_0603_1608Metric,1,C15849
22uF 25V,C3,C_1206_3216Metric,1,C12891
470nF,C32,C_0402_1005Metric,1,C47339
1.2pF,"C29,C30,C38,C39,C40,C41",C_0402_1005Metric,6,C327292
10uF,"C20,C43",C_0603_1608Metric,2,C19702
100nF,"C11,C21,C34,C35,C36,C44",C_0402_1005Metric,6,C1525
10nF,"C19,C31,C33,C46",C_0402_1005Metric,4,C15195
10pF,"C27,C28,C37,C50,C51",C_0402_1005Metric,5,C32949
1uF,"C18,C22,C25,C26,C42,C45,C49,C8,C9",C_0402_1005Metric,9,C52923
B5819WS,"D2,D3",D_SOD-323,2,C7420331
green,D4,LED_0603_1608Metric,1,C72043
2450FM07D0034T,FL1,2450FM07D0034,1,C2651081
ZH1.5 4P (ESC),J1,JST_ZH_B4B-ZR-SM4-TF_1x04-1MP_P1.50mm_Vertical,1,C265083
U.FL (ELRS),J10,U.FL_Hirose_U.FL-R-SMT-1_Vertical,1,C88374
U.FL (receiver WiFi),J11,U.FL_Hirose_U.FL-R-SMT-1_Vertical,1,C88374
U.FL (brain WiFi),J12,U.FL_Hirose_U.FL-R-SMT-1_Vertical,1,C88374
SH1.0 4P (VTX),J3,JST_SH_BM04B-SRSS-TB_1x04-1MP_P1.00mm_Vertical,1,C160390
ZH1.5 2P (fan),J4,JST_ZH_B2B-ZR-SM4-TF_1x02-1MP_P1.50mm_Vertical,1,C265284
ZH1.5 2P (IR LED),J5,JST_ZH_B2B-ZR-SM4-TF_1x02-1MP_P1.50mm_Vertical,1,C265284
ZH1.5 2P (battery),J6,JST_ZH_B2B-ZR-SM4-TF_1x02-1MP_P1.50mm_Vertical,1,C265284
USB-C,J9,USB_C_Receptacle_HRO_TYPE-C-31-M-12,1,C165948
15uH,L5,L_0805_2012Metric,1,C486333
3nH,"L4,L6,L7",L_0402_1005Metric,3,C269824
2nH,"L2,L8",L_0402_1005Metric,2,C43365
24nH,"L3,L9",L_0402_1005Metric,2,C74301
AO3401,Q2,SOT-23,1,C15127
AO3400,"Q3,Q4",SOT-23,2,C20917
5.1k,"R12,R13",R_0402_1005Metric,2,C25905
22k,R15,R_0402_1005Metric,1,C25768
220,"R16,R17",R_0402_1005Metric,2,C25091
1k,"R18,R19,R20,R30,R4",R_0402_1005Metric,5,C11702
47k,R3,R_0402_1005Metric,1,C25792
10k,"R11,R25,R26,R27,R28,R29,R34",R_0402_1005Metric,7,C25744
33,R6,R_0805_2012Metric,1,C17634
100,R7,R_0402_1005Metric,1,C25076
100k,"R14,R2,R31,R32,R5,R8",R_0402_1005Metric,6,C25741
ESP32-C3FH4,"U1,U5",QFN-32-1EP_5x5mm_P0.5mm_EP3.7x3.7mm,2,C2858491
AP2112K-3.3,"U3,U8",SOT-23-5,2,C51118
SX1280IMLTRT,U6,QFN-24-1EP_4x4mm_P0.5mm_EP2.6x2.6mm,1,C125969
AT2401C,U7,QFN-16-1EP_3x3mm_P0.5mm_EP1.7x1.7mm,1,C783588
52MHz,Y2,Crystal_SMD_2016-4Pin_2.0x1.6mm,1,C841202
40MHz,"Y1,Y3",Crystal_SMD_2016-4Pin_2.0x1.6mm,2,C49158179

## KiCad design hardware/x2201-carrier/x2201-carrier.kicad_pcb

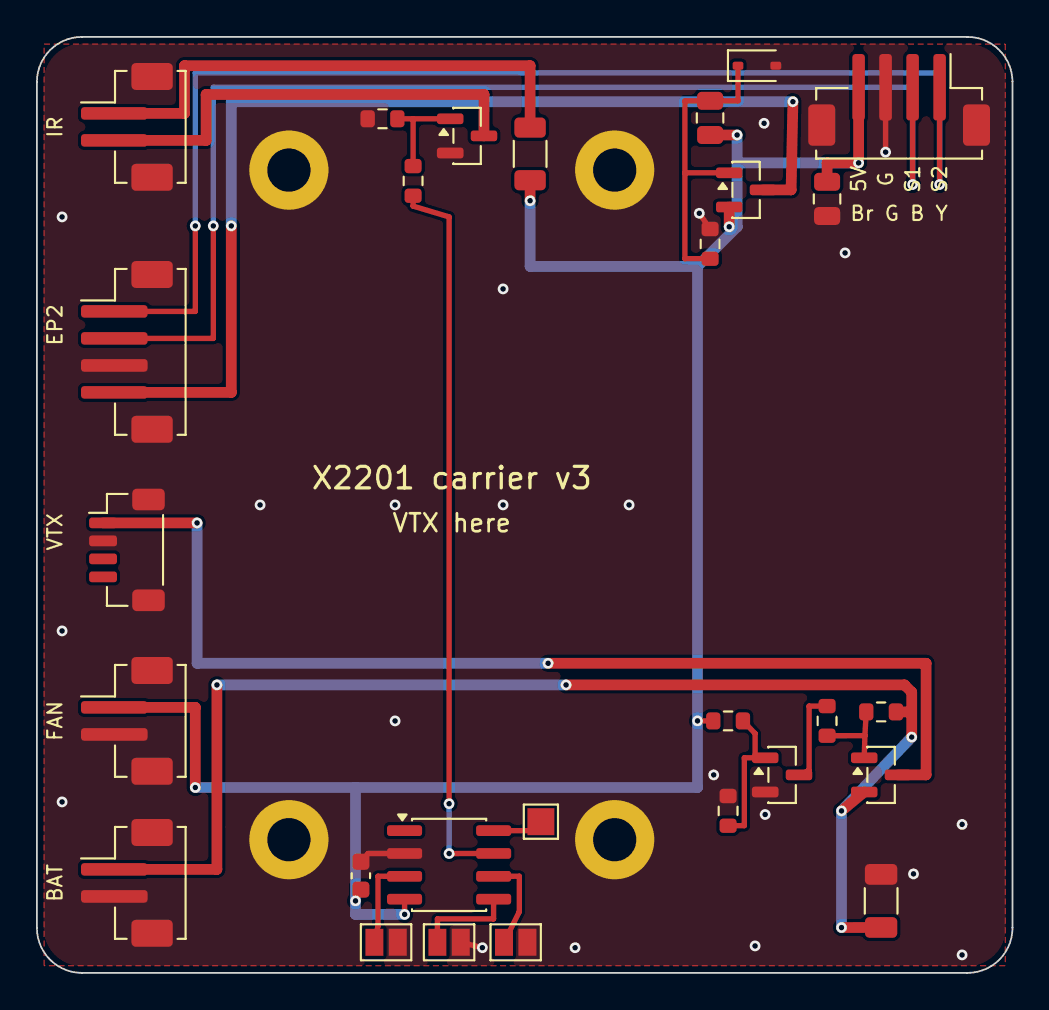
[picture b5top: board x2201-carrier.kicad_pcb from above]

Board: 2 copper layers, 54.2 x 52.0 mm, 32 parts (0 on the bottom side), 19 nets.

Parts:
C1: 10uF; C_0805_2012Metric
C2: 22uF; C_0805_2012Metric
C3: 22uF 25V; C_1206_3216Metric
C4: 100nF; C_0603_1608Metric
D1: 1N4148WS; D_SOD-323
H1, H2, H3, H4: M2 SMT nut
J1: ZH1.5 4P (ESC); JST_ZH_B4B-ZR-SM4-TF_1x04-1MP_P1.50mm_Vertical
J2: ZH1.5 4P (EP2); JST_ZH_B4B-ZR-SM4-TF_1x04-1MP_P1.50mm_Vertical
J3: SH1.0 4P (VTX); JST_SH_BM04B-SRSS-TB_1x04-1MP_P1.00mm_Vertical
J4: ZH1.5 2P (fan); JST_ZH_B2B-ZR-SM4-TF_1x02-1MP_P1.50mm_Vertical
J5: ZH1.5 2P (IR LED); JST_ZH_B2B-ZR-SM4-TF_1x02-1MP_P1.50mm_Vertical
J6: ZH1.5 2P (battery); JST_ZH_B2B-ZR-SM4-TF_1x02-1MP_P1.50mm_Vertical
JP1: ID0; SolderJumper-2_P1.3mm_Open_Pad1.0x1.5mm
JP2: ID1; SolderJumper-2_P1.3mm_Open_Pad1.0x1.5mm
JP3: ID2; SolderJumper-2_P1.3mm_Open_Pad1.0x1.5mm
Q1, Q2: AO3401; SOT-23
Q3, Q4: AO3400; SOT-23
R1, R2, R5, R8: 100k; R_0603_1608Metric
R3: 47k; R_0603_1608Metric
R4: 1k; R_0603_1608Metric
R6: 33; R_1206_3216Metric
R7: 100; R_0603_1608Metric
TP11: SWIO; TestPoint_Pad_1.5x1.5mm
U2: CH32V003J4M6; SOIC-8_3.9x4.9mm_P1.27mm

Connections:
5V: C1.1, C2.1, C4.2, J1.4, J4.1, Q1.2, R4.1, R6.2, U2.4
GATE: Q4.1, R7.2, R8.2
GND: C2.2, C3.2, C4.1, D1.2, H1.1, H2.1, H3.1, H4.1, J1.3, J1.MP, J2.3, J2.MP, J3.2, J3.MP, J4.2, J4.MP, J5.MP, J6.2, J6.MP, JP1.2, JP2.2, JP3.2, Q3.2, Q4.2, R1.2, R5.2, R8.1, U2.2
ID0: JP1.1, U2.5
ID1: JP2.1, U2.6
ID2: JP3.1, U2.3
LEDA: J5.1, R6.1
LEDK: J5.2, Q4.3
PWM: R7.1, U2.7
Q2G: Q2.1, R2.1, R3.1
Q3D: Q3.3, R3.2
Q3G: Q3.1, R4.2, R5.1
RX5V: J2.4, Q1.3
RXG: C1.2, D1.1, Q1.1, R1.1
S1: J1.2, J2.2
S2: J1.1, J2.1
SWIO: TP11.1, U2.8
VBAT: C3.1, J6.1, Q2.2, R2.2
VTX: J3.1, Q2.3

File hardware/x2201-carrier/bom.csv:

Comment,Designator,Footprint,Qty,LCSC Part #
10uF,C1,C_0805_2012Metric,1,C15850
22uF,C2,C_0805_2012Metric,1,C45783
22uF 25V,C3,C_1206_3216Metric,1,C12891
100nF,C4,C_0603_1608Metric,1,C14663
1N4148WS,D1,D_SOD-323,1,C2128
M2 SMT nut,"H1,H2,H3,H4",,4,
ZH1.5 4P (ESC),J1,JST_ZH_B4B-ZR-SM4-TF_1x04-1MP_P1.50mm_Vertical,1,C265083
ZH1.5 4P (EP2),J2,JST_ZH_B4B-ZR-SM4-TF_1x04-1MP_P1.50mm_Vertical,1,C265083
SH1.0 4P (VTX),J3,JST_SH_BM04B-SRSS-TB_1x04-1MP_P1.00mm_Vertical,1,C160390
ZH1.5 2P (fan),J4,JST_ZH_B2B-ZR-SM4-TF_1x02-1MP_P1.50mm_Vertical,1,C265284
ZH1.5 2P (IR LED),J5,JST_ZH_B2B-ZR-SM4-TF_1x02-1MP_P1.50mm_Vertical,1,C265284
ZH1.5 2P (battery),J6,JST_ZH_B2B-ZR-SM4-TF_1x02-1MP_P1.50mm_Vertical,1,C265284
AO3401,"Q1,Q2",SOT-23,2,C15127
AO3400,"Q3,Q4",SOT-23,2,C20917
47k,R3,R_0603_1608Metric,1,C25819
1k,R4,R_0603_1608Metric,1,C21190
33,R6,R_1206_3216Metric,1,
100,R7,R_0603_1608Metric,1,C22775
100k,"R1,R2,R5,R8",R_0603_1608Metric,4,C25803
CH32V003J4M6,U2,SOIC-8_3.9x4.9mm_P1.27mm,1,C5299908

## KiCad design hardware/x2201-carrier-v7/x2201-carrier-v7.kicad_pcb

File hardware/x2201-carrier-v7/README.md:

# X2201 載板 v7（ESP32-S3-Zero + EP2）

47×30 mm，2 層，1.6 mm，單面零件，4 個 M2 不鍍銅孔（孔距 42×25）。

只做這些事：**電池電量偵測、計圈、讓 EP2 上電就能工作、接線**，並接上圖傳 UART，供之後做 OSD。

訊號鏈：`EP2 → CRSF → S3-Zero → PWM → 電調`。EP2 不再直接接電調，R11 再把它的 TX 腳拉高，這就是上電卡死的解法。

## 下單

| 項目 | 內容 |
|---|---|
| PCB | 上傳 `x2201-carrier-v7-gerber.zip`：2 層、1.6 mm、1 oz |
| 元件 | `bom.csv` 上的料號，全部可在立創商城買到 |
| 模組 | ESP32-S3-Zero、EP2 2400RX 各一 |
| 插頭線 | ZH1.5 4P ×1、ZH1.5 2P ×3（圖傳用它原裝的 SH1.0 線） |

## 手焊順序

位置看 `x2201-carrier-v7-assembly.png`，零件編號對照 `bom.csv`。

1. MOS（Q2 是 AO3401，Q3、Q4 是 AO3400）和二極體 D3。
2. 所有 0805 阻容。
3. 插座：先焊 J3（SH1.0，腳距最小），再焊 J1、J4、J5、J6。
4. 先量：5V、VBAT、3V3 對 GND 都不能短路。
5. 焊 S3-Zero：USB 朝板邊，對齊 18 個焊盤。
6. 焊 EP2：貼在絲印框內，四個焊盤用短線橋接到板上 TX / RX / 5V / G，**依名稱對應，不要只看位置**。

## 接法

| 位號 | 類型 | 腳位 |
|---|---|---|
| J1 電調 | ZH1.5 4P | 1 S2 黃、2 S1 藍、3 GND 綠、4 5V 棕 |
| J3 圖傳 | SH1.0 4P | 1 電源、2 GND、3 圖傳 RX、4 圖傳 TX |
| J4 風扇 | ZH1.5 2P | 1 5V、2 GND，電調一開就轉 |
| J5 IR | ZH1.5 2P | 1 LED+、2 LED− |
| J6 電池 | ZH1.5 2P | 1 VBAT、2 GND |

圖傳的電池電源由電調的 5V 控制（Q2、Q3）：電調開關關掉，圖傳也會斷電。

| GPIO | 功能 |
|---|---|
| 4 | IR |
| 5 / 6 | CRSF RX / TX |
| 7 / 8 | 電調 S2 / S1 |
| 9 | 電池電壓（×22/122） |
| 11 / 12 | 圖傳 UART TX / RX（MSP OSD） |

## 第一次上電

上電測試在 [firmware/elrs-bench](../../firmware/elrs-bench/README.md)，韌體的接腳和這塊板相同。

- D3 會擋住 USB 流進電調 BEC，焊好後可以同時插 USB 和電調。
- J1 的線序（第 1 腳是 S2）還要對照實車確認。

## 重新產生

```bash
/Applications/KiCad/KiCad.app/Contents/Frameworks/Python.framework/Versions/Current/bin/python3 gen_pcb.py
```

佈線用 `../tools/freerouting-1.9.0.jar`；沒有這個檔案時加 `REUSE_SES=1`，沿用已存的 `.ses`。`FAB=1` 同時輸出 Gerber 和 BOM，之後再跑 `gen_sch.py` 更新原理圖。

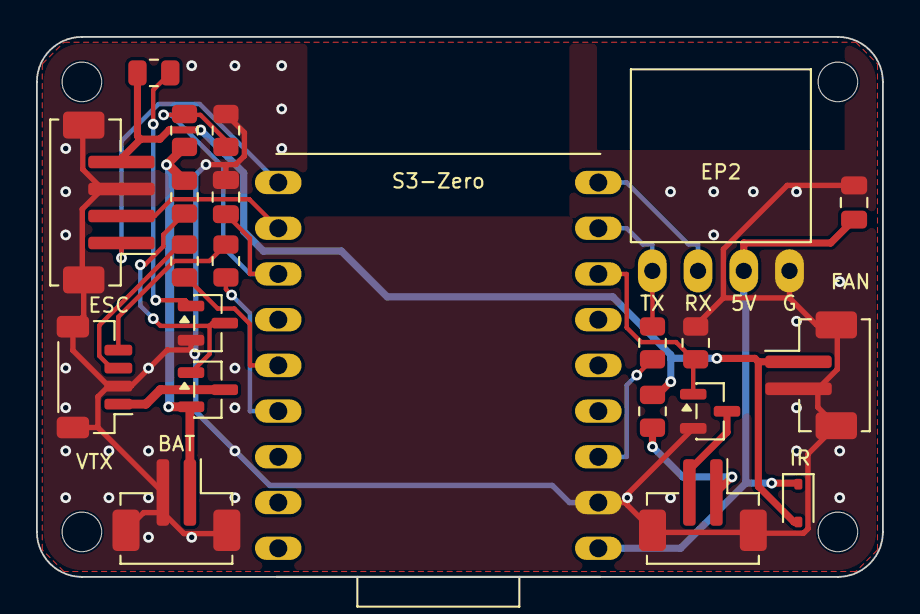
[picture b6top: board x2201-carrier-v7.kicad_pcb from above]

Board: 2 copper layers, 47.0 x 30.0 mm, 26 parts (0 on the bottom side), 20 nets.

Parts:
C10: 22uF; C_0805_2012Metric
C11: 100nF; C_0805_2012Metric
D3: B5819WS; D_SOD-323
J1: ZH1.5 4P (ESC); JST_ZH_B4B-ZR-SM4-TF_1x04-1MP_P1.50mm_Vertical
J3: SH1.0 4P (VTX); JST_SH_BM04B-SRSS-TB_1x04-1MP_P1.00mm_Vertical
J4: ZH1.5 2P (fan); JST_ZH_B2B-ZR-SM4-TF_1x02-1MP_P1.50mm_Vertical
J5: ZH1.5 2P (IR LED); JST_ZH_B2B-ZR-SM4-TF_1x02-1MP_P1.50mm_Vertical
J6: ZH1.5 2P (battery); JST_ZH_B2B-ZR-SM4-TF_1x02-1MP_P1.50mm_Vertical
MH1, MH2, MH3, MH4: M2 hole
Q2: AO3401; SOT-23
Q3, Q4: AO3400; SOT-23
R2, R8, R14: 100k; R_0805_2012Metric
R4, R19, R20: 1k; R_0805_2012Metric
R6: 33; R_0805_2012Metric
R11: 10k; R_0805_2012Metric
R15: 22k; R_0805_2012Metric
U1: ESP32-S3-Zero
U2: EP2 2400RX; EP2_2400RX

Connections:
3V3: R11.1, U1.3V3
5V: D3.2, J1.4, J4.1, R4.1, R6.2
5VM: C10.1, D3.1, U1.5V, U2.5V
CRSF_RX: R11.2, U1.5, U2.TX
CRSF_TX: U1.6, U2.RX
GND: C10.2, C11.2, J1.3, J1.MP, J3.2, J3.MP, J4.2, J4.MP, J5.MP, J6.2, J6.MP, Q3.2, Q4.2, R8.2, R15.2, U1.GND, U2.G
IR: Q4.1, R8.1, U1.4
LEDA: J5.1, R6.1
LEDK: J5.2, Q4.3
MSP_RX: R20.1, U1.12
MSP_TX: R19.1, U1.11
Q2G: Q2.1, Q3.3, R2.1
Q3G: Q3.1, R4.2
S1: J1.2, U1.8
S2: J1.1, U1.7
VBAT: J6.1, Q2.2, R2.2, R14.1
VBAT_ADC: C11.1, R14.2, R15.1, U1.9
VTX: J3.1, Q2.3
VTX_RX: J3.3, R19.2
VTX_TX: J3.4, R20.2

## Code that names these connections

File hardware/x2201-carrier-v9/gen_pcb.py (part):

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
# ---- U1: ESP32-S3-MINI-1, antenna at the top edge ------------------------------------------
CX, CY = 21.3, 14.2
GPIO = {3: "3V3", 4: "BOOT", 10: "VTX_EN", 11: "THR", 12: "SERVO", 13: "VBAT_ADC", 14: "MSP_RX", 15: "MSP_TX",  # IO6..IO11
        17: "CRSF_RX", 18: "CRSF_TX", 19: "IR", 20: "SDA", 21: "SCL", 22: "IMU_INT",  # bottom row: IO13..IO18
        23: "USB_DM", 24: "USB_DP", 45: "EN"}
U1_NETS = {str(k): v for k, v in GPIO.items()}
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

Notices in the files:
parts and their libraries:
From AnyLeaf elrs-hardware (MIT, (c) 2023 AnyLeaf LLC). https://www.johansontechnology.com/datasheets/2450FM07D0034/2450FM07D0034.pdf
